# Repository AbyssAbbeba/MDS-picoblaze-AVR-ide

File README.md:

# MDS-picoblaze-AVR-ide
Picoblaze IDE - simulator, compiler, dissassembler and more

MDS provides all the necessary functionality to develop software part of a PicoBlaze application, including source code editor,
assembler, disassembler, and simulator. Besides that there is also a number of tools and functions to make your work easier,
the sole purpose of MDS is to save your time and enable development of more complex applications.

## Main features

  -  Text editor optimized for writing source code.
  -  Project manager for creating and maintaining your projects.
  -  Very fast simulator for all available versions of Picoblaze.
  -  Macro-assembler supporting wide range of output file formats, including MEM, HEX, and VHDL.
  -  PicoBlaze disassembler capable of reading from HEX, VHDL, MEM, and other file formats.
  -  Tool called Assembler Translator for compatibility with your current tools.
  -  Command line tools, and a number of graphical utilities.
  
## Assembler  
MDS macro-assembler for PicoBlaze is a two stage fast macro-assembler inspired by Intel assemblers and the C language. It supports
wide range of output data formats and a number of advanced features like macro processing, conditions, loops, etc. it is
meant to give you means to write code with run-time efficiency typical for the assembly language while giving you some of the comfort
of a more high-level language like C. 

Quick user guide:
https://moravia-microsystems.net/mds/others/QuickUserGuideAssembler.pdf

For instance you may use: 
 - if ( S0 == S1 ) to easy write conditions instead of compares and conditional jumps
 - for ( S0, 0 .. 9 ) for loops
 - #if my_constant > 20 for conditional compilation
 - abc macro x, y, z for defining your own macros, and more. 

  MDS assembler is enhanced with these features in hope it will help you save your time and make your work a little bit easier.
  MDS assembler also has a number of features for smooth and transparent debugging and it is regularly subjected to extensive automated
  testing to ensure its very functionality and to provide high reliability. Also this assembler supports all PicoBlaze versions
  publicly available at the time of its release. For these reasons we are convinced that this is the most advanced assembler 
  for PicoBlaze currently available on the market.
  
## Tutorial and example project  
  The aim of the tutorial project is to provide an easy way to explore the IDE without reading long documents. The tutorial project
  can be opened from the [Main Menu] -> [Help] -> [Tutorial Project].
  
  Demonstration project should introduce a new user into the basics of usage of this IDE, this generally
  covers the most common functions like assembling the code, running simulator, and so on.

  ## Requirements
  
  This software is compiled for x86 processors in both 32b and 64b variants with SSE instruction set, that means you need a processor equipped with SEE feature (most processors manufactured after the year 2003 are). For GNU/Linux, MDS also requires GLIBC version >= 2.17.

Supported host operating systems are:

   - Microsoft Windows 7 (32b and 64b),
   - Microsoft Windows XP (32b),
   - Ubuntu 13.10 and higher (32b and 64b),
   - CentOS 7 (64b),
   - openSUSE 13.1 and higher (32b and 64b),
   - Fedora 20 and higher (32b and 64b).
   
  ## Precompiled versions:
  
 https://moravia-microsystems.net/

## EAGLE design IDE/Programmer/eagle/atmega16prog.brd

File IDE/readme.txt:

== Introduction ==
Every directory should contain a readme.txt file describing its content; and, if
possible, also a CMakeLists.txt file to compile whatever is in the directory.

== Instructions ==
 * cmake .	<-- generate Makefile(s); on Windows, it is 'cmake -G "MSYS Makefiles"'
 * make		<-- compile the source codes
 * make doc	<-- use doxygen to generate API documentation
 * make test	<-- run automated tests
 * make package	<-- generate installation packages

== Common conventions ==
(this should be discussed on some meeting...)

== Required software ==

=== On Windows ===
 - MinGW (+MSYS)
 - CMake
 - gitk (when installing, choose "Run Git and included Unix tools from the Windows command prompt")
 - Doxygen

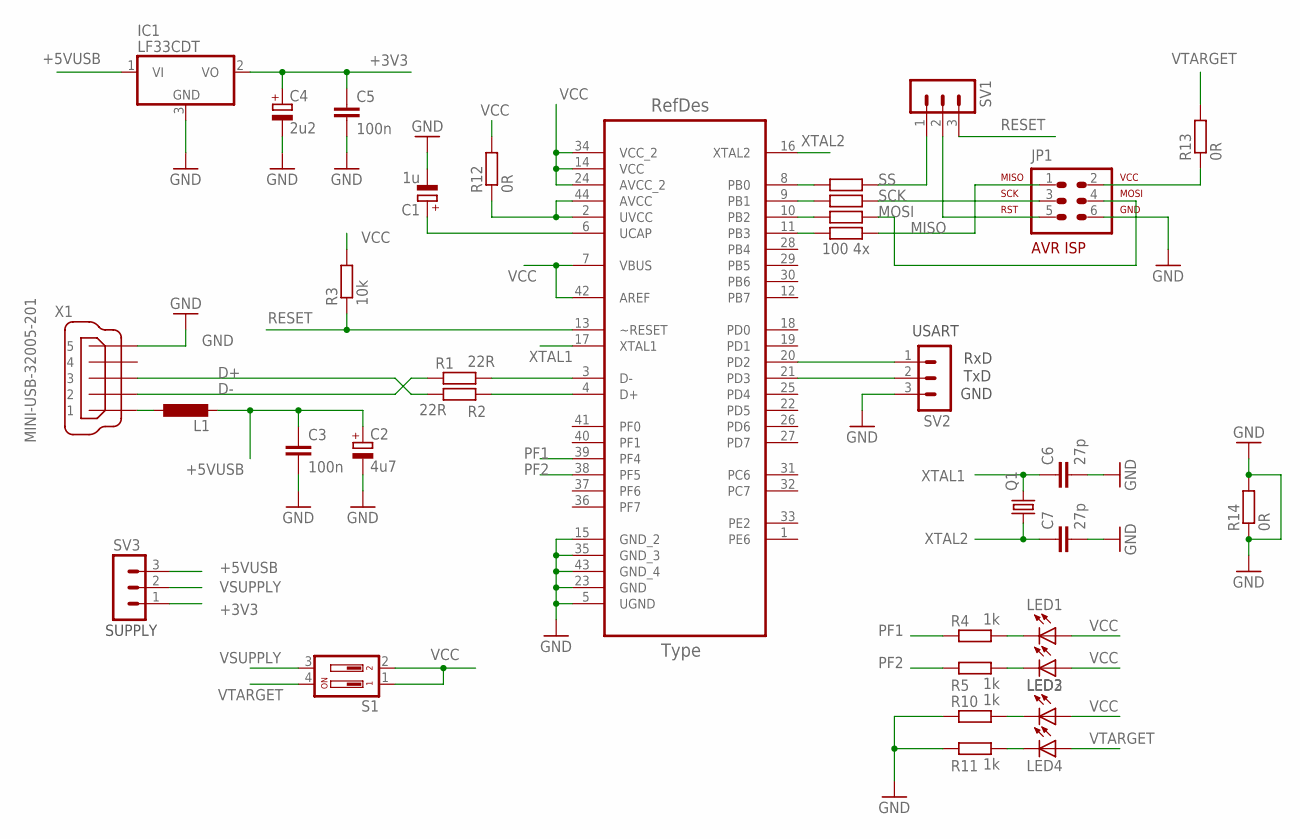
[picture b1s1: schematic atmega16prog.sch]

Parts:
C1: 1u; SMC_A
C2: 4u7; SMC_B
C3, C5: 100n; C0805K
C4: 2u2; A/3216-18W
C6, C7: 27p; C0805K
IC1: LF33CDT; TO252
JP1: AVR-ISP-6VERT; AVR-ISP-6
L1: L-EU0204/7; 0204/7
LED1, LED2, LED3, LED4: LED3MM
Q1: CRYSTALHC49S; HC49/S
R1, R2: 22R; M0805
R3: 10k; M0805
R4, R5, R10, R11: 1k; M0805
R6: 100 4x; M0805
R7: R-EU_R0805; R0805
R8: R-EU_M0805; M0805
R9: 100; M0805
R12, R13, R14: 0R; MINI_MELF-0102W
S1: DS02; DS-02
SV1, SV2, SV3: MA03-1
U1: ATMEGA16U4-AU; QFP80P1200X1200X120-44N
X1: MINI-USB-32005-201; 32005-201

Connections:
+3V3: C4.+, C5.1, IC1.2 (VO), SV3.1
+5VUSB: C2.+, C3.1, IC1.1 (VI), L1.2, SV3.3
D+: R2.1, X1.3
D-: R1.1, X1.2
GND: C1.-, C2.-, C3.2, C4.-, C5.2, C6.2, C7.2, IC1.3 (GND), JP1.6, R10.1, R11.1, R14.1, R14.2, SV2.3, U1.5 (UGND), U1.15 (GND_2), U1.23 (GND), U1.35 (GND_3), U1.43 (GND_4), X1.5
MISO: JP1.1, R6.2
MOSI: JP1.4, R7.2
unnamed: C1.+, U1.6 (UCAP)
unnamed: SV2.1, U1.20 (PD2)
unnamed: R2.2, U1.4 (D+)
unnamed: R1.2, U1.3 (D-)
unnamed: R9.1, U1.8 (PB0)
unnamed: R8.1, U1.9 (PB1)
unnamed: SV2.2, U1.21 (PD3)
unnamed: LED1.K (C), R4.2
unnamed: LED2.K (C), R5.2
unnamed: R7.1, U1.10 (PB2)
unnamed: R6.1, U1.11 (PB3)
unnamed: L1.1, X1.1
unnamed: LED3.K (C), R10.2
unnamed: LED4.K (C), R11.2
unnamed: R12.1, U1.2 (UVCC), U1.44 (AVCC)
unnamed: JP1.2, R13.1
PF1: R4.1, U1.39 (PF4)
PF2: R5.1, U1.38 (PF5)
RESET: R3.1, SV1.3, U1.13 (~RESET)
RST: JP1.5, SV1.2
SCK: JP1.3, R8.2
SS: R9.2, SV1.1
VCC: LED1.A, LED2.A, LED3.A, R3.2, R12.2, S1.1, S1.2, U1.7 (VBUS), U1.14 (VCC), U1.24 (AVCC_2), U1.34 (VCC_2), U1.42 (AREF)
VSUPPLY: S1.3, SV3.2
VTARGET: LED4.A, R13.2, S1.4
XTAL1: C6.1, Q1.2, U1.17 (XTAL1)
XTAL2: C7.1, Q1.1, U1.16 (XTAL2)

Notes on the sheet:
GND
TxD
RxD
USART
SUPPLY

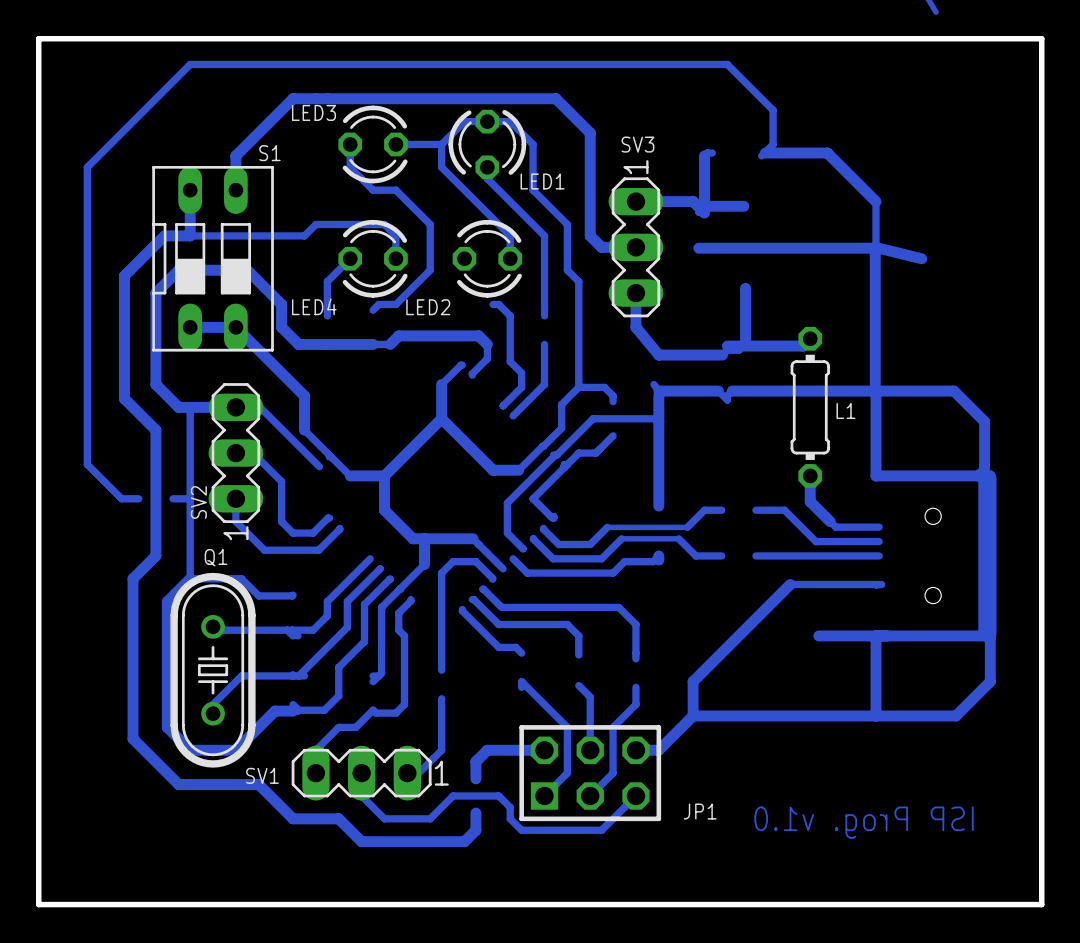
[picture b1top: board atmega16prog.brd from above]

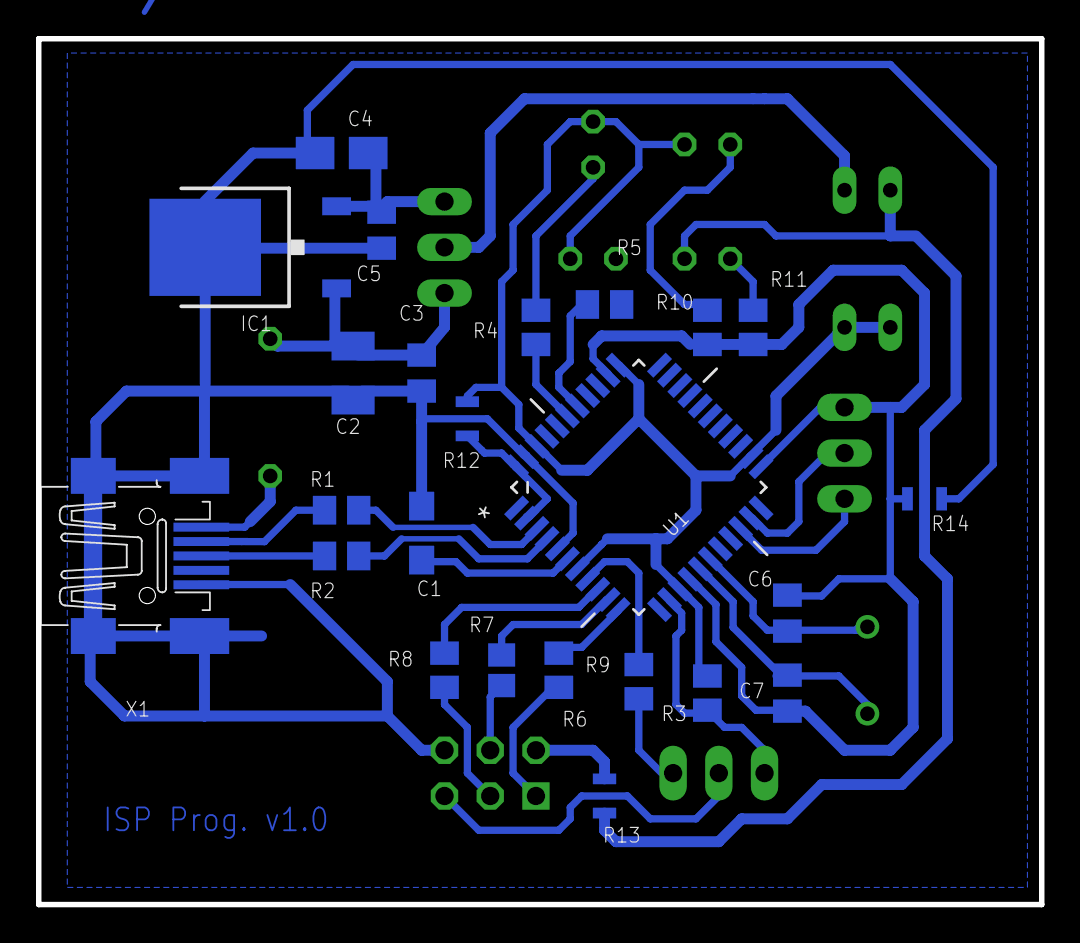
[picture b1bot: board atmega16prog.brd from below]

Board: 2 copper layers, 55.7 x 48.1 mm, 35 parts (24 on the bottom side), 34 nets.

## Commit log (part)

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2015-01-15 +gui
2015-01-15 (no comment)
2018-06-30 Master: git publish version
2018-06-30 Fix refund policy
2018-07-03 Add missing license and reference to icons
2018-07-05 Created readme file
2018-07-05 Readme added assembler quick user guide
2018-07-06 Added picture to readme
